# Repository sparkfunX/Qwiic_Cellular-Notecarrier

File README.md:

SparkFun Qwiic Cellular Notecarrier - Blues Wireless
========================================

[*SparkX Qwiic Cellular Notecarrier (SPX-17114)*](https://www.sparkfun.com/products/17114)

When we first saw the Notecard from [Blues Wireless](https://blues.io/) we were intrigued. Unlike most embedded cellular modems, the price of the Blues Wireless card includes a 10 year subscription and 500MB of data. A global cellular module with a built in SIM card with no monthly fee? That sounds enticing. After all, the last thing we need is a hot water heater monitor with a monthly cell phone bill!

The power of Qwiic just keeps expanding! Simply plug the Qwiic Cellular Notecarrier onto any enabled SparkFun Qwiic platforms (currently [over 30](https://www.sparkfun.com/qwiic#products)) and you’ll be able to transmit data anywhere there is cell connectivity with a few lines of Python, Arduino, or JSON. The Blues documentation is superb. All [API calls](https://dev.blues.io/reference/notecard-api/) come with extensive C, Python, and JSON examples. While the Qwiic Cellular focuses on using the I2C bus for communication, USB and Serial can also be used to communicate with the Notecard. We found the USB was handy for immediate gratification and command debugging.

The Notecard module comes with integrated cellular, SIM, onboard GPS, accelerometer, and temperature sensor. The Qwiic Cellular product has everything you need: a carrier board (Blues calls them Notepads), the globally enabled [NB-IoT & LTE-M](https://shop.blues.io/products/note-nbgl-500) M.2 based module (Blues calls them Notecards), and two U.FL cables all assembled and ready to go.

Currently 139 countries are covered with another 33 countries covered by installing a user-supplied external SIM socket and card. See the [Covered Countries](https://dev.blues.io/hardware/notecard-datasheet/note-nbgl-500/#cellular-and-gps-gnss-antenna-requirements) table for more information. Two RF cables connect the Notecard to external SMA connectors for cellular and GPS antennas (sold separately in related items below).

SparkFun labored with love to create this code. Feel like supporting open source hardware? 
Buy a [board](https://www.sparkfun.com/products/17114) from SparkFun!

Repository Contents
-------------------

* **/hardware** - Eagle files

Documentation
--------------

* **[Quick Start Guide](https://dev.blues.io/get-started/quickstart/sparkfun-qwiic-cellular)**
* **[Installing an Arduino Library Guide](https://learn.sparkfun.com/tutorials/installing-an-arduino-library)** - Basic information on how to install an Arduino library.
* **[Notecard API](https://dev.blues.io/reference/notecard-api/introduction/)** - How to interface with Notecard from embedded processor applciations
* **[Notecard Design Files](https://github.com/blues/note-hardware/tree/master/Notecard)** - Models and dimensioned drawings of Notecard

Products that use this Repository
--------------

* [SPX-17114](https://www.sparkfun.com/products/17114)

License Information
-------------------

This product is _**open source**_! 

Please review the LICENSE.md file for license information. 

If you have any questions or concerns on licensing, please contact technical support on our [SparkFun forums](https://forum.sparkfun.com/viewforum.php?f=152).

Distributed as-is; no warranty is given.

- Your friends at SparkFun.

_<COLLABORATION CREDIT>_

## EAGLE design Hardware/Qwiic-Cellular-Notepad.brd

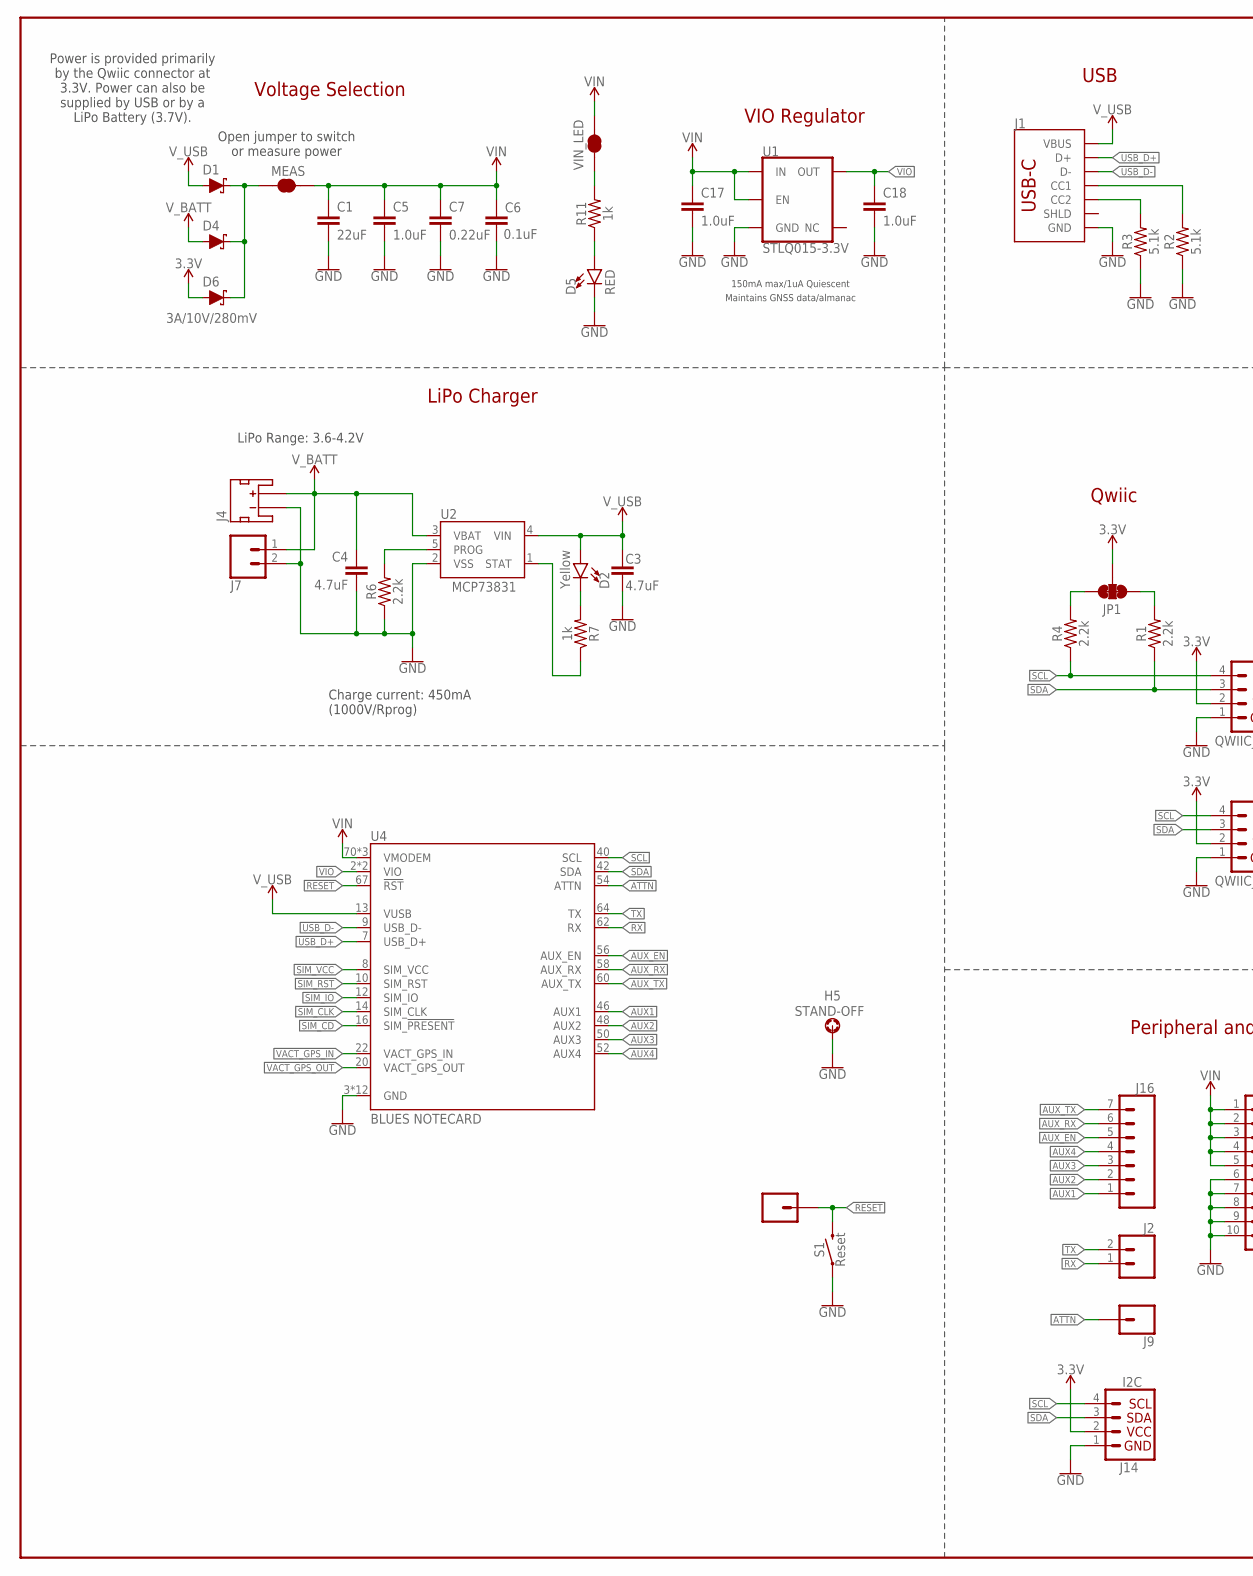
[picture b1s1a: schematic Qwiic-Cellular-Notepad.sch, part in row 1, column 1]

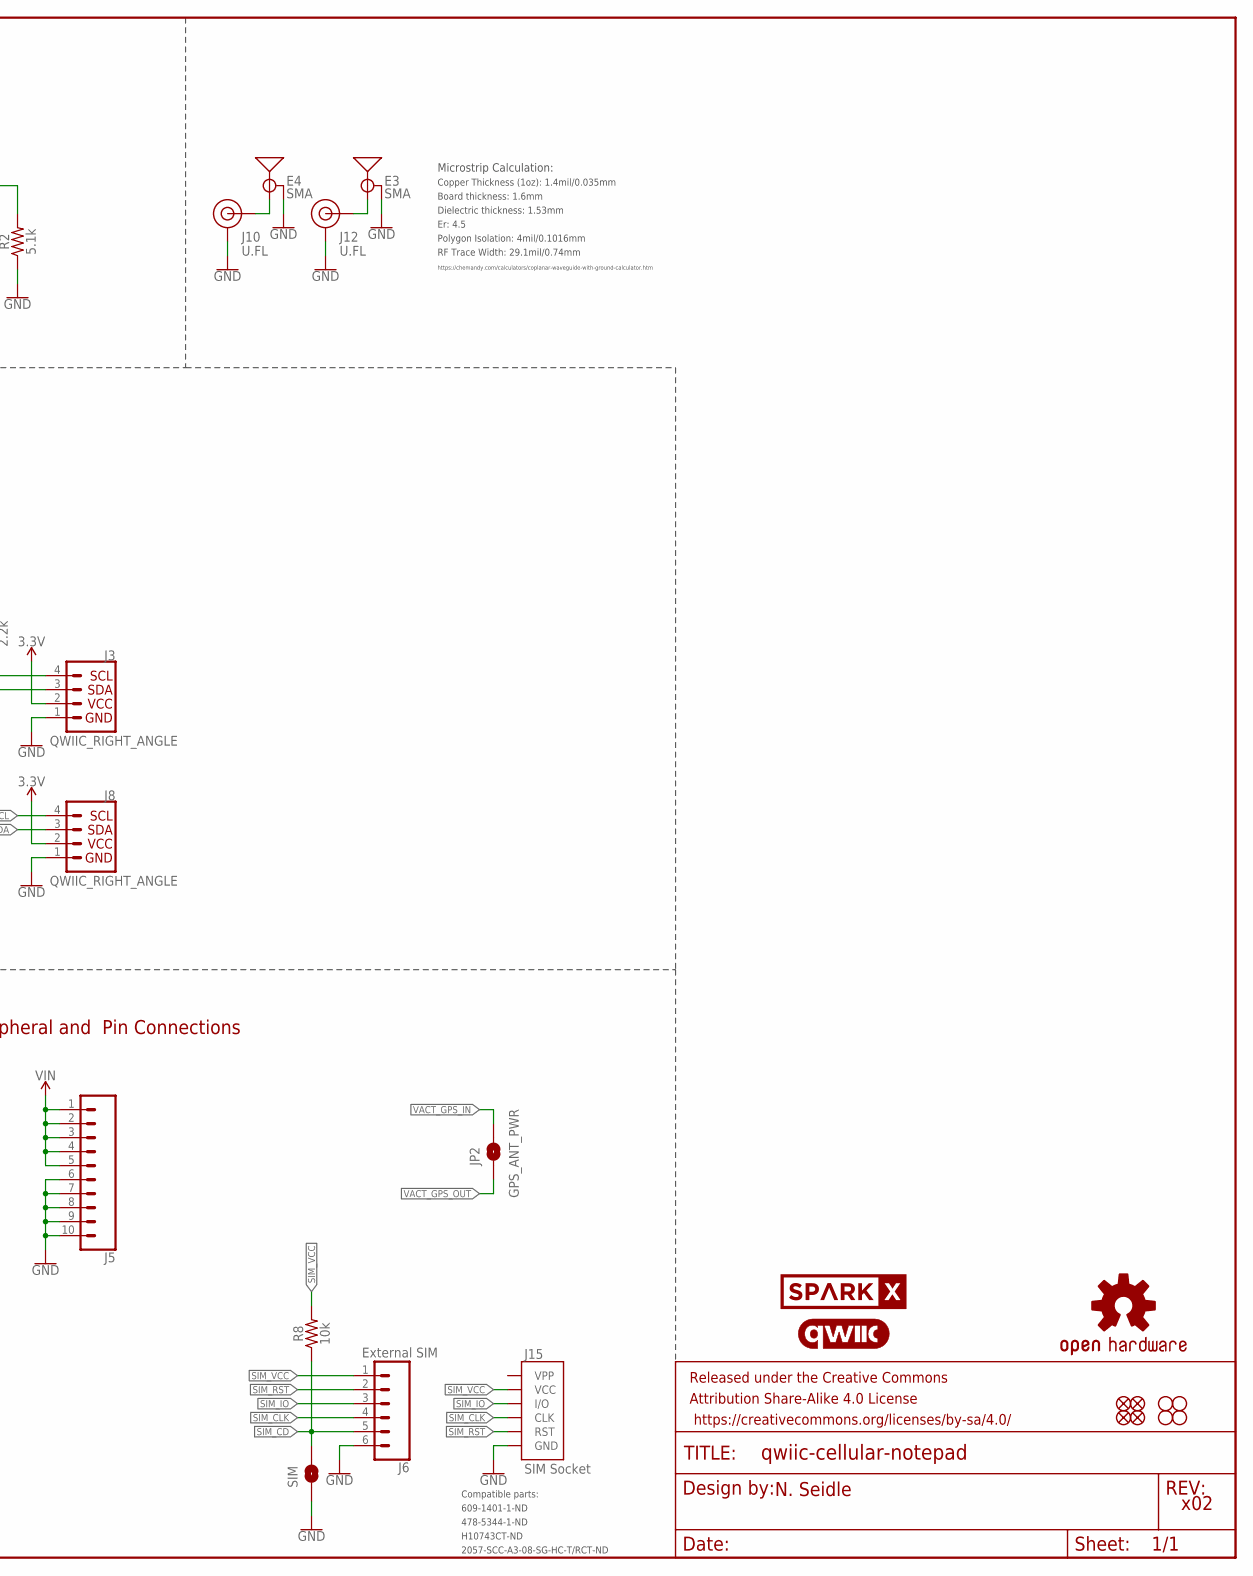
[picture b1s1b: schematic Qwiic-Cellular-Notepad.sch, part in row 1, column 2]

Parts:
C1: 22uF; 1210
C3, C4: 4.7uF; 0603
C5, C17, C18: 1.0uF; 0603
C6: 0.1uF; 0603
C7: 0.22uF; 0603
D1, D4, D6: 3A/10V/280mV; SOD-323
D2: Yellow; LED-0603
D5: RED; LED-0603
E3, E4: SMA; SMA-EDGE-SMD
FD1, FD2, FD3, FD4: FIDUCIALUFIDUCIAL; FIDUCIAL-MICRO
FRAME1: FRAME-LEDGER; CREATIVE_COMMONS
H1, H2, H3, H4: STAND-OFF
H5: STAND-OFF; STAND-OFF-REFLOW-M2.5
J1: USB_C_2-LAYER_PADS; USB-C-16P-2LAYER-PADS
J2, J7: CONN_021X02_NO_SILK; 1X02_NO_SILK
J3, J8: QWIIC_RIGHT_ANGLE; JST04_1MM_RA
J4: JST_2MM_MALE; JST-2-SMD
J5: CONN_10NO_SILK_PTH_FEMALE; 1X10_NO_SILK
J6: External SIM; 1X06_NO_SILK
J9, J13: CONN_01PTH_NO_SILK_YES_STOP; 1X01_NO_SILK
J10, J12: U.FL
J14: I2C; 1X04_NO_SILK
J15: SIM Socket; SIMHOLDER
J16: CONN_07NO_SILK; 1X07_NO_SILK
JP1: JUMPER-SMT_3_2-NC_TRACE_SILK; SMT-JUMPER_3_2-NC_TRACE_SILK
JP2: GPS_ANT_PWR; SMT-JUMPER_2_NO_SILK
LOGO2: QWIIC_LOGO_CONNECTOR; QWIIC_5.5MM
LOGO3: OSHW-LOGOMINI; OSHW-LOGO-MINI
MEAS: JUMPER-COMBO_2_NC_TRACE; COMBO-JUMPER_2_NC_TRACE
R1, R4, R6: 2.2k; 0603
R2, R3: 5.1k; 0603
R7, R11: 1k; 0603
R8: 10k; 0603
S1: Reset; TACTILE_SWITCH_SMD_5.2MM
SIM: JUMPER-SMT_2_NO_SILK; SMT-JUMPER_2_NO_SILK
U1: STLQ015-3.3V; SOT23-5
U2: MCP73831; SOT23-5
U4: BLUES NOTECARD; M.2-CONNECTOR-E
U$56: SPARKX-LOGO4; SPARKX-MEDIUM
VIN_LED: JUMPER-SMT_2_NC_TRACE_SILK; SMT-JUMPER_2_NC_TRACE_SILK

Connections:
3.3V: D6.A, J3.2, J8.2, J14.2, JP1.2
!RESET!: J13.1, S1.3 (2), S1.4 (2), U4.67 (!RST!)
ATTN: J9.1, U4.54 (ATTN)
AUX1: J16.1, U4.46 (AUX1)
AUX2: J16.2, U4.48 (AUX2)
AUX3: J16.3, U4.50 (AUX3)
AUX4: J16.4, U4.52 (AUX4)
AUX_EN: J16.5, U4.56 (AUX_EN)
AUX_RX: J16.6, U4.58 (AUX_RX)
AUX_TX: J16.7, U4.60 (AUX_TX)
CHG_LED: R7.1, U2.1 (STAT)
GND: C1.2, C3.2, C4.2, C5.2, C6.2, C7.2, C17.2, C18.2, D5.C, E3.GND@0 (GND), E3.GND@1 (GND), E4.GND@0 (GND), E4.GND@1 (GND), H5.1, J1.GND, J1.GND2 (GND), J3.1, J4.1 (-), J5.6, J5.7, J5.8, J5.9, J5.10, J6.6, J7.2, J8.1, J10.1 (GND), J10.2 (GND), J12.1 (GND), J12.2 (GND), J14.1, J15.C5 (GND), R2.1, R3.1, R6.1, S1.1, S1.2 (1), SIM.1, U1.2 (GND), U2.2 (VSS), U4.3 (GND), U4.5 (GND), U4.6 (GND), U4.11 (GND), U4.18 (GND), U4.33 (GND), U4.39 (GND), U4.45 (GND), U4.51 (GND), U4.57 (GND), U4.71 (GND), U4.73 (GND)
unnamed: JP1.3, R4.2
unnamed: JP1.1, R1.2
unnamed: D2.C, R7.2
unnamed: D5.A, R11.1
unnamed: R11.2, VIN_LED.1
unnamed: R6.2, U2.5 (PROG)
unnamed: J1.A5 (CC1), R2.2
unnamed: J1.B5 (CC2), R3.2
RF_GPS: E4.SIG (SIGNAL), J10.FEED (SIGNAL)
RF_LTE: E3.SIG (SIGNAL), J12.FEED (SIGNAL)
RX: J2.1, U4.62 (RX)
SCL: J3.4, J8.4, J14.4, R4.1, U4.40 (SCL)
SDA: J3.3, J8.3, J14.3, R1.1, U4.42 (SDA)
SIM_!CD!: J6.5, R8.1, SIM.2, U4.16 (SIM_!PRESENT!)
SIM_CLK: J6.4, J15.C3 (CLK), U4.14 (SIM_CLK)
SIM_IO: J6.3, J15.C7 (I/O), U4.12 (SIM_IO)
SIM_RST: J6.2, J15.C2 (RST), U4.10 (SIM_RST)
SIM_VCC: J6.1, J15.C1 (VCC), R8.2, U4.8 (SIM_VCC)
TX: J2.2, U4.64 (TX)
USB_D+: J1.A6 (D+), J1.B6 (D+), U4.7 (USB_D+)
USB_D-: J1.A7 (D-), J1.B7 (D-), U4.9 (USB_D-)
VACT_GPS_IN: JP2.2, U4.22 (VACT_GPS_IN)
VACT_GPS_OUT: JP2.1, U4.20 (VACT_GPS_OUT)
VIN: C1.1, C5.1, C6.1, C7.1, C17.1, J5.1, J5.2, J5.3, J5.4, J5.5, MEAS.2, MEAS.4 (2), U1.1 (IN), U1.3 (EN), U4.70 (VMODEM), U4.72 (VMODEM), U4.74 (VMODEM), VIN_LED.2
VIN1: D1.C, D4.C, D6.C, MEAS.1, MEAS.3 (1)
VIO: C18.1, U1.5 (OUT), U4.2 (VIO), U4.4 (VIO)
V_BATT: C4.1, D4.A, J4.2 (+), J7.1, U2.3 (VBAT)
V_USB: C3.1, D1.A, D2.A, J1.VBUS1 (VBUS), J1.VBUS2 (VBUS), U2.4 (VIN), U4.13 (VUSB)

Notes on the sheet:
USB
Peripheral and Pin Connections
Qwiic
Voltage Selection
LiPo Charger
LiPo Range: 3.6-4.2V
Charge current: 450mA (1000V/Rprog)
Open jumper to switch or measure power
N. Seidle
x02
Power is provided primarily by the Qwiic connector at 3.3V. Power can also be supplied by USB or by a LiPo Battery (3.7V).
Board thickness: 1.6mm
Er: 4.5
Copper Thickness (1oz): 1.4mil/0.035mm
RF Trace Width: 29.1mil/0.74mm
Polygon Isolation: 4mil/0.1016mm
Dielectric thickness: 1.53mm
https://chemandy.com/calculators/coplanar-waveguide-with-ground-calculator.htm
Microstrip Calculation:
Compatible parts:
609-1401-1-ND
478-5344-1-ND
H10743CT-ND
2057-SCC-A3-08-SG-HC-T/RCT-ND
VIO Regulator
150mA max/1uA Quiescent
Maintains GNSS data/almanac

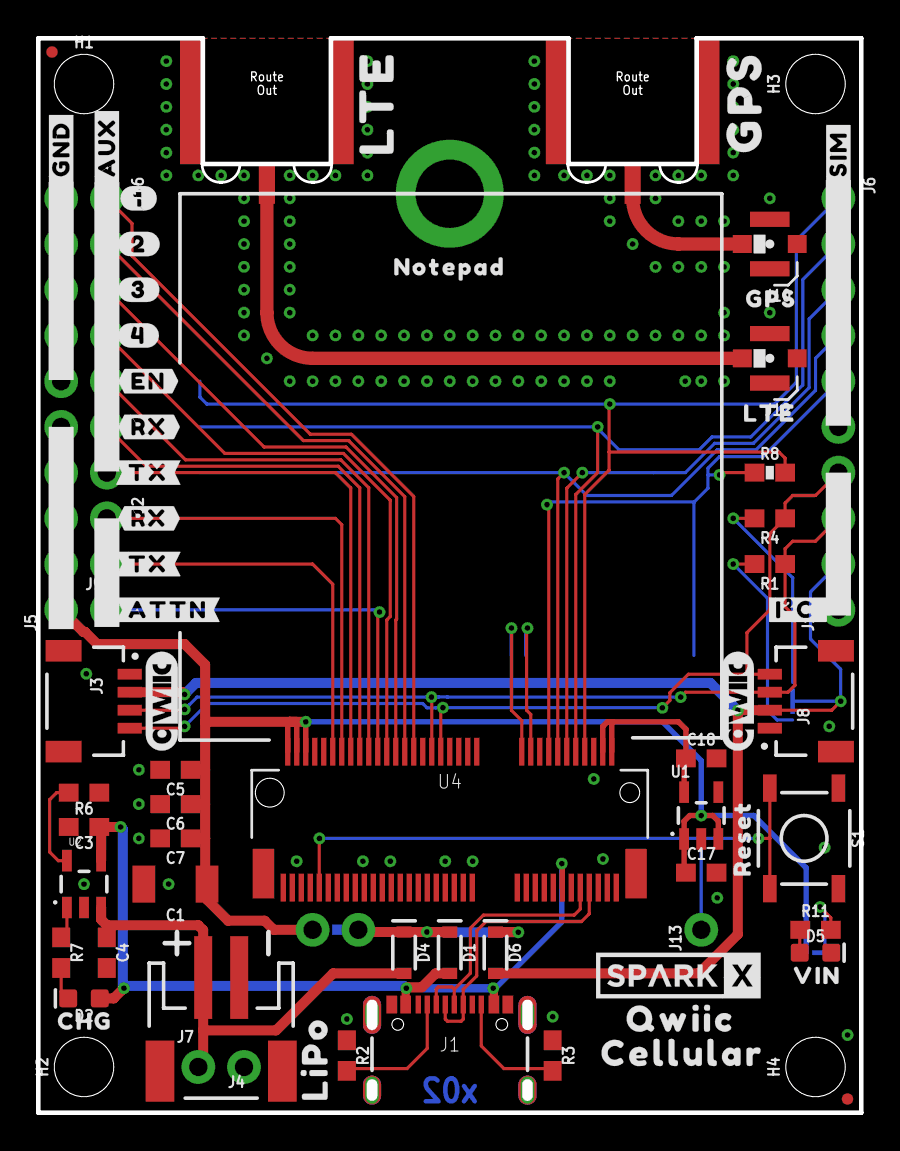
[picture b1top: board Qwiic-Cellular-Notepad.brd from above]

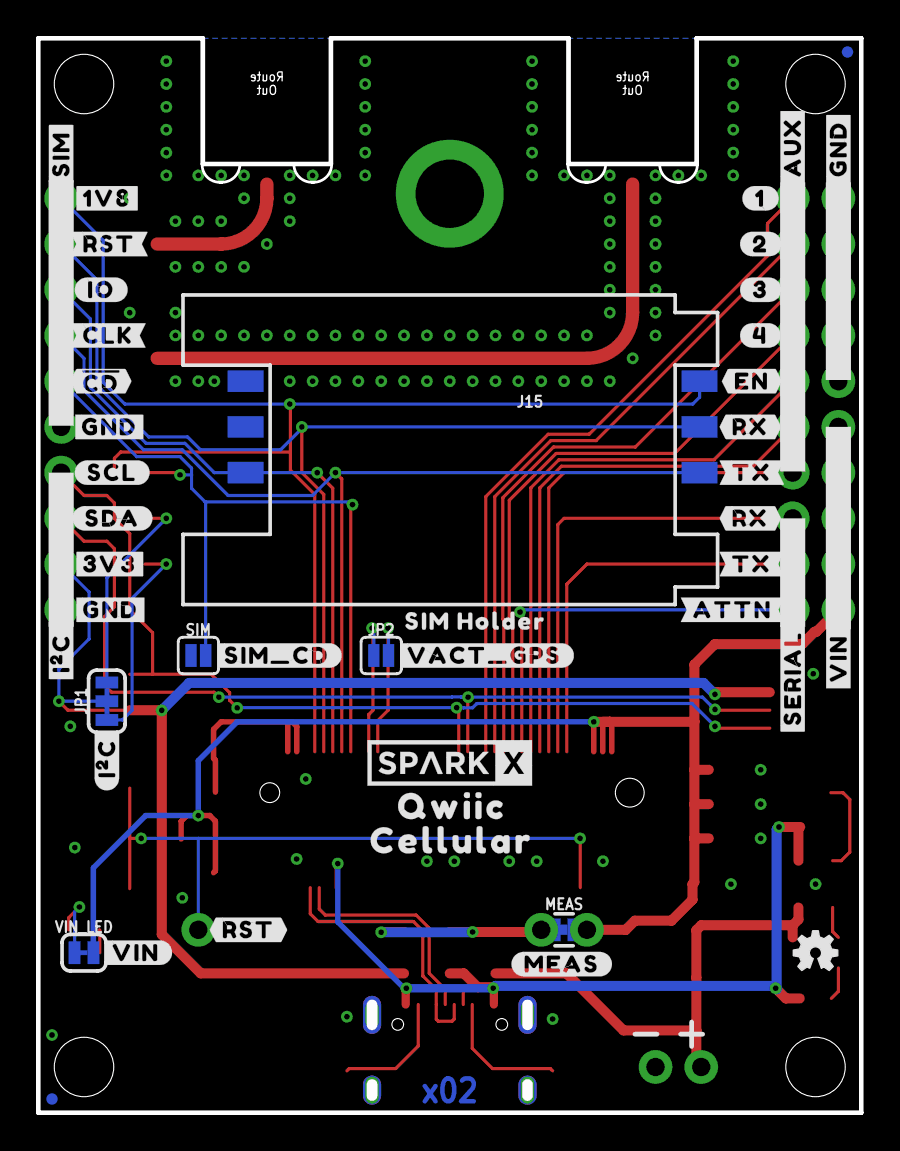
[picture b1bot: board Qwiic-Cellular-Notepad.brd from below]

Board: 2 copper layers, 45.7 x 59.7 mm, 122 parts (45 on the bottom side), 40 nets.

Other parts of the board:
LOGO5: QWIIC_LOGO_CONNECTOR; QWIIC_5.5MM
U$1, U$41: #1#1
U$2: #3V3#2
U$3, U$18, U$22: #GND#0
U$4, U$42: #2#2
U$5, U$43: #3#3
U$6, U$44: #4#4
U$7: GPS_0
U$8: #SERIAL#1
U$9, U$53: #I�C_#0
U$10: #I�C#0
U$11, U$40: #AUX#0
U$12: LTE_1
U$13: #GND#3
U$14, U$46: #RX#6
U$15: LIPO0
U$16, U$47: #TX#5
U$17: #SCL#1
U$19, U$45: #EN#0
U$20: NOTEPAD0
U$21: #SDA#0
U$23: #VIN#0
U$24: #VACT_GPS#0
U$25: #SIM_CD#0
U$26, U$31: QWIIC0
U$27: SIM_HOLDER0
U$28: #MEAS#3
U$29, U$32: CELLULAR1
U$30: #RST#0
U$33: #VIN#1
U$34: ##CD##1
U$35: #1V8#4
U$36: #CLK#3
U$37: #IO#2
U$38: #RST#5
U$39, U$51: #SIM#0
U$48, U$52: #RX#0
U$49, U$54: #TX#1
U$50, U$55: #ATTN#2
U$57: SPARKX-LOGO4; SPARKX-MEDIUM
U$58: GPS0
U$59: LTE1
U$92: RESET1
U$94: VIN1
U$96: CHG1

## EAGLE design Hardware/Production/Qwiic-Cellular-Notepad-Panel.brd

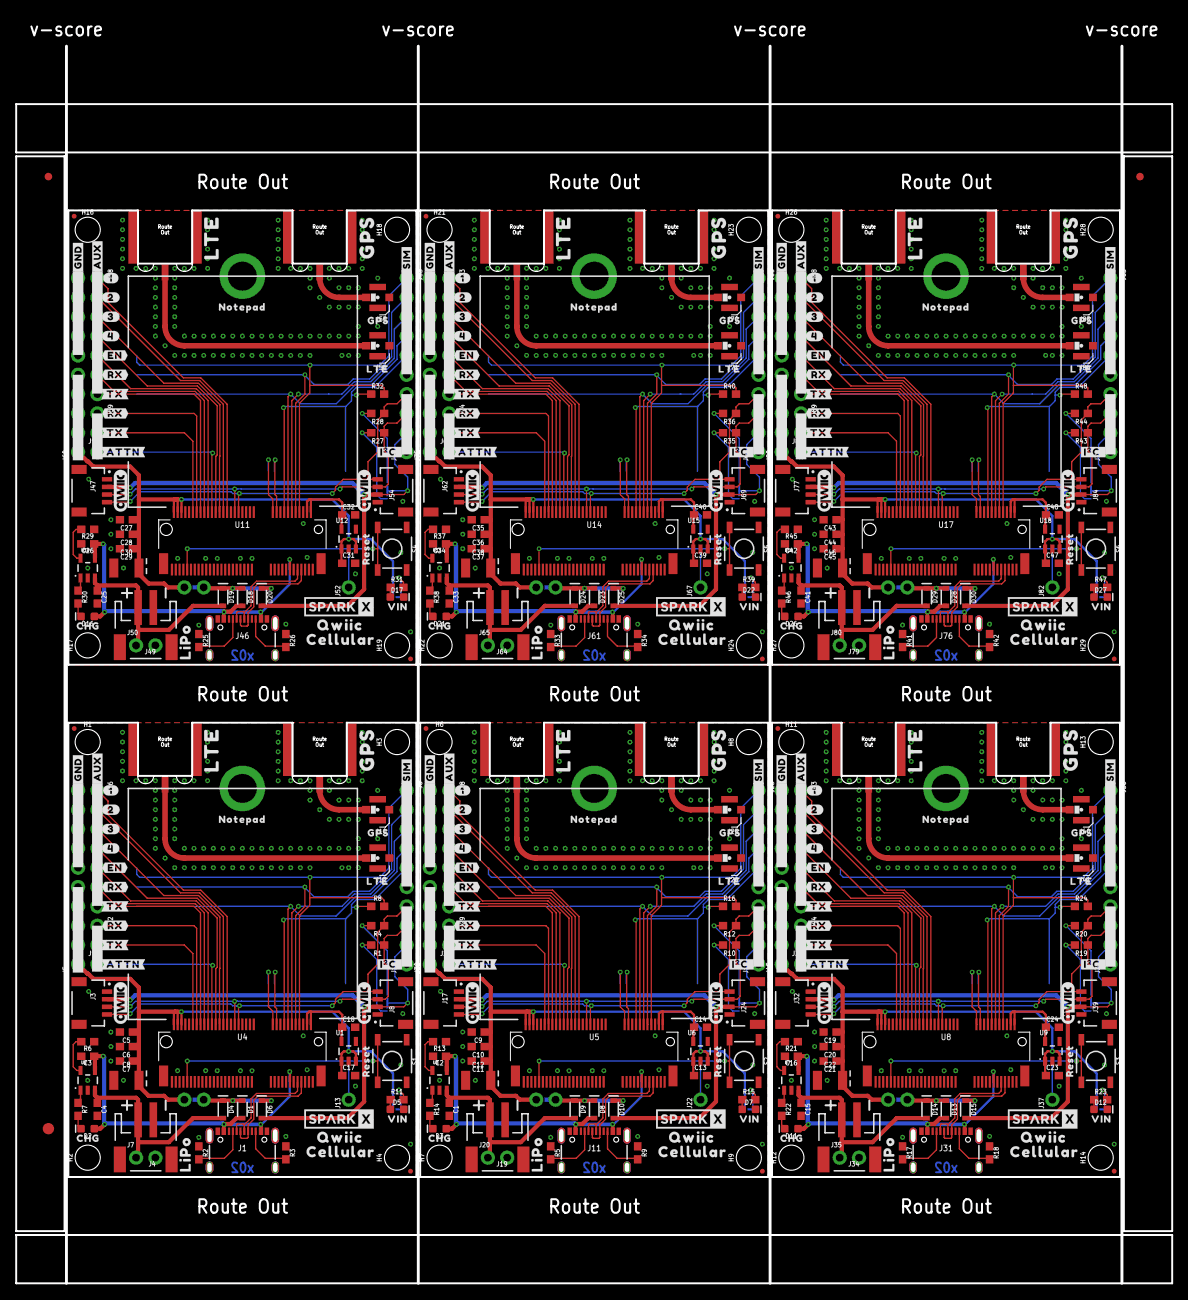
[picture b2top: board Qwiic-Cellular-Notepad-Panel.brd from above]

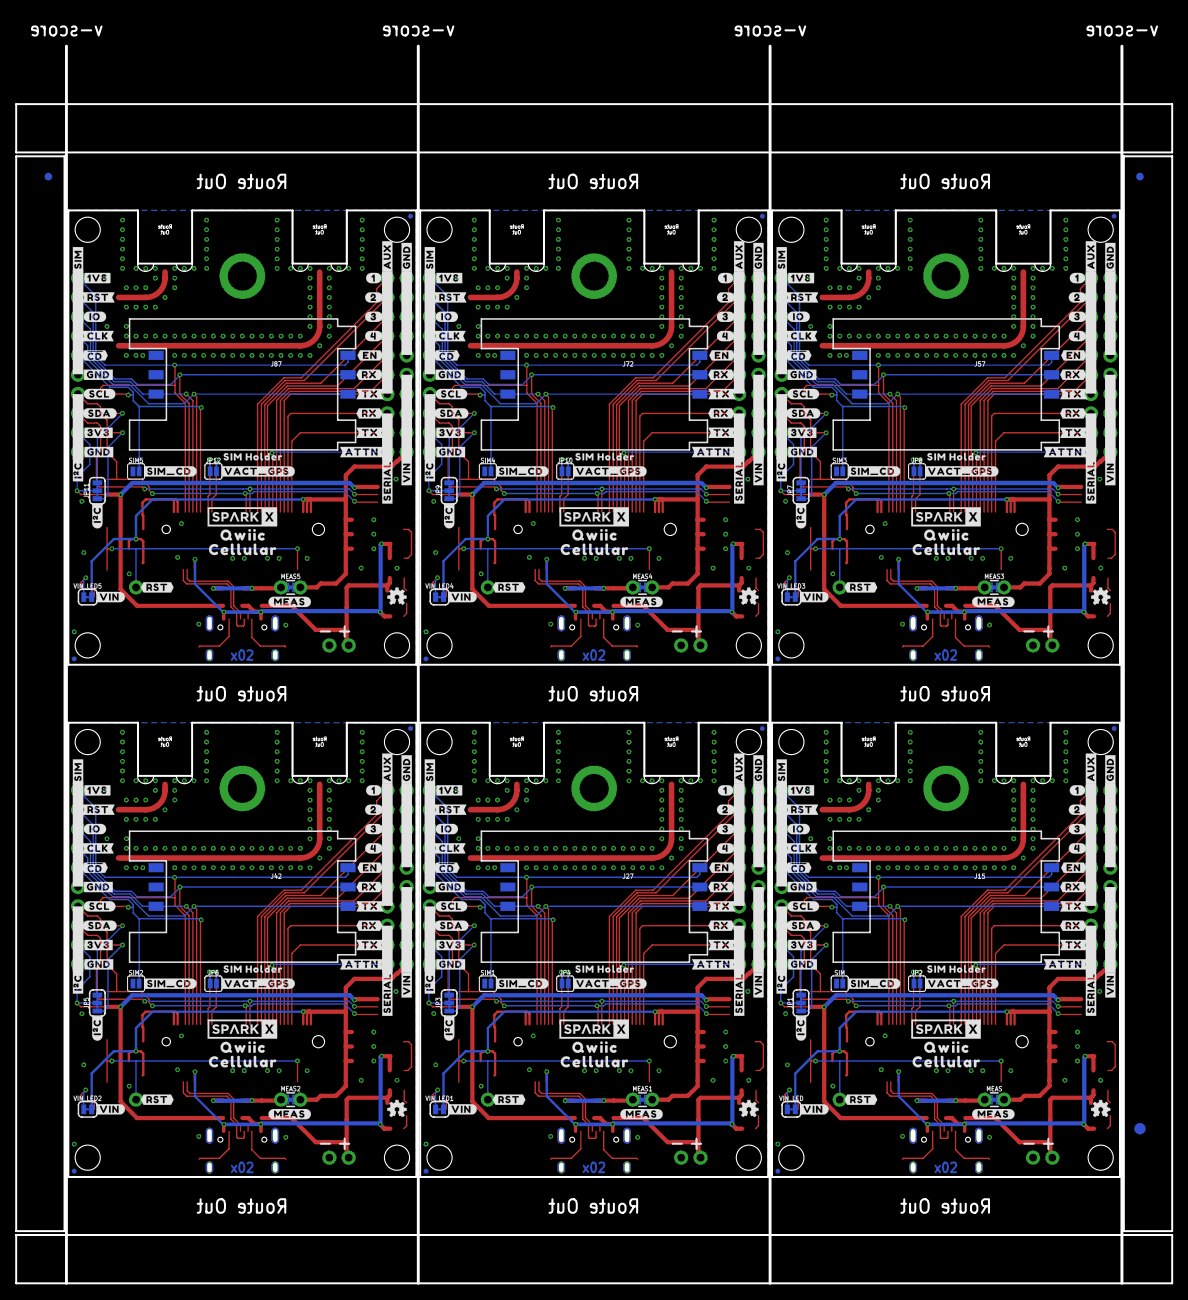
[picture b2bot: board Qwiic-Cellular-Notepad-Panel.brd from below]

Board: 2 copper layers, 151.9 x 162.6 mm, 732 parts (273 on the bottom side), 240 nets.

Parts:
C1, C2, C3, C4, C15, C16, C25, C26, C33, C34, C41, C42: 4.7uF; 0603
C5, C9, C13, C14, C17, C18, C19, C23, C24, C27, C31, C32, C35, C39, C40, C43, C47, C48: 1.0uF; 0603
C6, C10, C20, C28, C36, C44: 0.1uF; 0603
C7, C11, C21, C29, C37, C45: 0.22uF; 0603
C8, C12, C22, C30, C38, C46: 68uF; EIA3528
D1, D4, D6, D8, D9, D10, D13, D14, D15, D18, D19, D20, D23, D24, D25, D28, D29, D30: 3A/10V/280mV; SOD-323
D2, D3, D11, D16, D21, D26: Yellow; LED-0603
D5, D7, D12, D17, D22, D27: RED; LED-0603
E1, E2, E3, E4, E5, E6, E7, E8, E9, E10, E11, E12: SMA; SMA-EDGE-SMD
E$1, E$2, E$3, E$4: FIDUCIAL-1X2
E$5, E$6: FIDUCIAL-1.5X3
FD1, FD2, FD3, FD4, FD5, FD6, FD7, FD8, FD9, FD10, FD11, FD12, FD13, FD14, FD15, FD16, FD17, FD18, FD19, FD20, FD21, FD22, FD23, FD24: FIDUCIALUFIDUCIAL; FIDUCIAL-MICRO
H1, H2, H3, H4, H6, H7, H8, H9, H11, H12, H13, H14, H16, H17, H18, H19, H21, H22, H23, H24, H26, H27, H28, H29: STAND-OFF
H5, H10, H15, H20, H25, H30: STAND-OFF; STAND-OFF-REFLOW-M2.5
J1, J11, J31, J46, J61, J76: USB-C-16P-2LAYER-PADS
J2, J7, J20, J29, J35, J44, J50, J59, J65, J74, J80, J89: 1X02_NO_SILK
J3, J8, J17, J24, J32, J39, J47, J54, J62, J69, J77, J84: QWIIC_RIGHT_ANGLE; JST04_1MM_RA
J4, J19, J34, J49, J64, J79: JST-2-SMD
J5, J30, J45, J60, J75, J90: 1X10_NO_SILK
J6, J23, J38, J53, J68, J83: External SIM; 1X06_NO_SILK
J9, J13, J21, J22, J36, J37, J51, J52, J66, J67, J81, J82: 1X01_NO_SILK
J10, J12, J25, J26, J40, J41, J55, J56, J70, J71, J85, J86: U.FL
J14, J18, J33, J48, J63, J78: I2C; 1X04_NO_SILK
J15, J27, J42, J57, J72, J87: SIM Socket; SIMHOLDER
J16, J28, J43, J58, J73, J88: 1X07_NO_SILK
JP1, JP3, JP5, JP7, JP9, JP11: SMT-JUMPER_3_2-NC_TRACE_SILK
JP2, JP4, JP6, JP8, JP10, JP12: GPS_ANT_PWR; SMT-JUMPER_2_NO_SILK
LOGO1, LOGO2, LOGO5, LOGO6, LOGO7, LOGO9, LOGO10, LOGO12, LOGO13, LOGO15, LOGO16, LOGO18: QWIIC_LOGO_CONNECTOR; QWIIC_5.5MM
LOGO3, LOGO4, LOGO8, LOGO11, LOGO14, LOGO17: OSHW-LOGOMINI; OSHW-LOGO-MINI
MEAS, MEAS1, MEAS2, MEAS3, MEAS4, MEAS5: COMBO-JUMPER_2_NC_TRACE
R1, R4, R6, R10, R12, R13, R19, R20, R21, R27, R28, R29, R35, R36, R37, R43, R44, R45: 2.2k; 0603
R2, R3, R5, R9, R17, R18, R25, R26, R33, R34, R41, R42: 5.1k; 0603
R7, R11, R14, R15, R22, R23, R30, R31, R38, R39, R46, R47: 1k; 0603
R8, R16, R24, R32, R40, R48: 10k; 0603
S1, S2, S3, S4, S5, S6: Reset; TACTILE_SWITCH_SMD_5.2MM
SIM, SIM1, SIM2, SIM3, SIM4, SIM5: SMT-JUMPER_2_NO_SILK
U1, U6, U9, U12, U15, U18: STLQ015-3.3V; SOT23-5
U2, U3, U7, U10, U13, U16: MCP73831; SOT23-5
U4, U5, U8, U11, U14, U17: BLUES NOTECARD; M.2-CONNECTOR-E
U$1, U$41, U$83, U$111, U$148, U$173, U$210, U$235, U$272, U$297, U$334, U$359: #1#1
U$2, U$74, U$139, U$201, U$263, U$325: #3V3#2
U$3, U$18, U$22, U$63, U$73, U$109, U$128, U$138, U$171, U$190, U$200, U$233, U$252, U$262, U$295, U$314, U$324, U$357: #GND#0
U$4, U$42, U$84, U$112, U$149, U$174, U$211, U$236, U$273, U$298, U$335, U$360: #2#2
U$5, U$43, U$85, U$113, U$150, U$175, U$212, U$237, U$274, U$299, U$336, U$361: #3#3
U$6, U$44, U$86, U$114, U$151, U$176, U$213, U$238, U$275, U$300, U$337, U$362: #4#4
U$7, U$107, U$169, U$231, U$293, U$355: GPS_0
U$8, U$104, U$166, U$228, U$290, U$352: #SERIAL#1
U$9, U$53, U$106, U$122, U$168, U$184, U$230, U$246, U$292, U$308, U$354, U$370: #I�C_#0
U$10, U$105, U$167, U$229, U$291, U$353: #I�C#0
U$11, U$40, U$87, U$110, U$152, U$172, U$214, U$234, U$276, U$296, U$338, U$358: #AUX#0
U$12, U$108, U$170, U$232, U$294, U$356: LTE_1
U$13, U$75, U$140, U$202, U$264, U$326: #GND#3
U$14, U$46, U$88, U$116, U$153, U$178, U$215, U$240, U$277, U$302, U$339, U$364: #RX#6
U$15, U$64, U$129, U$191, U$253, U$315: LIPO0
U$16, U$47, U$89, U$117, U$154, U$179, U$216, U$241, U$278, U$303, U$340, U$365: #TX#5
U$17, U$76, U$141, U$203, U$265, U$327: #SCL#1
U$19, U$45, U$90, U$115, U$155, U$177, U$217, U$239, U$279, U$301, U$341, U$363: #EN#0
U$20, U$97, U$159, U$221, U$283, U$345: NOTEPAD0
U$21, U$77, U$142, U$204, U$266, U$328: #SDA#0
U$23, U$91, U$156, U$218, U$280, U$342: #VIN#0
U$24, U$78, U$143, U$205, U$267, U$329: #VACT_GPS#0
U$25, U$79, U$144, U$206, U$268, U$330: #SIM_CD#0
U$26, U$31, U$82, U$93, U$147, U$157, U$209, U$219, U$271, U$281, U$333, U$343: QWIIC0
U$27, U$80, U$145, U$207, U$269, U$331: SIM_HOLDER0
U$28, U$65, U$130, U$192, U$254, U$316: #MEAS#3
U$29, U$32, U$81, U$95, U$146, U$158, U$208, U$220, U$270, U$282, U$332, U$344: CELLULAR1
U$30, U$66, U$131, U$193, U$255, U$317: #RST#0
U$33, U$67, U$132, U$194, U$256, U$318: #VIN#1
U$34, U$99, U$161, U$223, U$285, U$347: ##CD##1
U$35, U$98, U$160, U$222, U$284, U$346: #1V8#4
U$36, U$100, U$162, U$224, U$286, U$348: #CLK#3
U$37, U$101, U$163, U$225, U$287, U$349: #IO#2
U$38, U$102, U$164, U$226, U$288, U$350: #RST#5
U$39, U$51, U$103, U$121, U$165, U$183, U$227, U$245, U$289, U$307, U$351, U$369: #SIM#0
U$48, U$52, U$68, U$118, U$133, U$180, U$195, U$242, U$257, U$304, U$319, U$366: #RX#0
U$49, U$54, U$69, U$119, U$134, U$181, U$196, U$243, U$258, U$305, U$320, U$367: #TX#1
U$50, U$55, U$70, U$120, U$135, U$182, U$197, U$244, U$259, U$306, U$321, U$368: #ATTN#2
U$56, U$57, U$123, U$124, U$185, U$186, U$247, U$248, U$309, U$310, U$371, U$372: SPARKX-LOGO4; SPARKX-MEDIUM
U$58, U$71, U$136, U$198, U$260, U$322: GPS0
U$59, U$72, U$137, U$199, U$261, U$323: LTE1
U$60, U$92, U$125, U$187, U$249, U$311: RESET1
U$61, U$94, U$126, U$188, U$250, U$312: VIN1
U$62, U$96, U$127, U$189, U$251, U$313: CHG1
VIN_LED, VIN_LED1, VIN_LED2, VIN_LED3, VIN_LED4, VIN_LED5: SMT-JUMPER_2_NC_TRACE_SILK

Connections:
3.3V: D6.A, J3.2, J8.2, J14.2, JP1.2
3.3V1: D10.A, J17.2, J18.2, J24.2, JP3.2
3.3V2: D15.A, J32.2, J33.2, J39.2, JP5.2
3.3V3: D20.A, J47.2, J48.2, J54.2, JP7.2
3.3V4: D25.A, J62.2, J63.2, J69.2, JP9.2
3.3V5: D30.A, J77.2, J78.2, J84.2, JP11.2
!RESET!: J13.1, S1.3, S1.4, U4.67
!RESET!1: J22.1, S2.3, S2.4, U5.67
!RESET!2: J37.1, S3.3, S3.4, U8.67
!RESET!3: J52.1, S4.3, S4.4, U11.67
!RESET!4: J67.1, S5.3, S5.4, U14.67
!RESET!5: J82.1, S6.3, S6.4, U17.67
ATTN: J9.1, U4.54
ATTN1: J21.1, U5.54
ATTN2: J36.1, U8.54
ATTN3: J51.1, U11.54
ATTN4: J66.1, U14.54
ATTN5: J81.1, U17.54
AUX1: J16.1, U4.46
AUX2: J16.2, U4.48
AUX3: J16.3, U4.50
AUX4: J16.4, U4.52
AUX5: J28.1, U5.46
AUX6: J28.2, U5.48
AUX7: J28.3, U5.50
AUX8: J28.4, U5.52
AUX9: J43.1, U8.46
AUX10: J43.2, U8.48
AUX11: J43.3, U8.50
AUX12: J43.4, U8.52
AUX13: J58.1, U11.46
AUX14: J58.2, U11.48
AUX15: J58.3, U11.50
AUX16: J58.4, U11.52
AUX17: J73.1, U14.46
AUX18: J73.2, U14.48
AUX19: J73.3, U14.50
AUX20: J73.4, U14.52
AUX21: J88.1, U17.46
AUX22: J88.2, U17.48
AUX23: J88.3, U17.50
AUX24: J88.4, U17.52
AUX_EN: J16.5, U4.56
AUX_EN1: J28.5, U5.56
AUX_EN2: J43.5, U8.56
AUX_EN3: J58.5, U11.56
AUX_EN4: J73.5, U14.56
AUX_EN5: J88.5, U17.56
AUX_RX: J16.6, U4.58
AUX_RX1: J28.6, U5.58
AUX_RX2: J43.6, U8.58
AUX_RX3: J58.6, U11.58
AUX_RX4: J73.6, U14.58
AUX_RX5: J88.6, U17.58
AUX_TX: J16.7, U4.60
AUX_TX1: J28.7, U5.60
AUX_TX2: J43.7, U8.60
AUX_TX3: J58.7, U11.60
AUX_TX4: J73.7, U14.60
AUX_TX5: J88.7, U17.60
CHG_LED: R7.1, U2.1
CHG_LED1: R14.1, U3.1
CHG_LED2: R22.1, U7.1
CHG_LED3: R30.1, U10.1
CHG_LED4: R38.1, U13.1
CHG_LED5: R46.1, U16.1
GND: C3.2, C4.2, C5.2, C6.2, C7.2, C8.C, C17.2, C18.2, D5.C, E3.GND@0, E3.GND@1, E4.GND@0, E4.GND@1, H5.1, J1.GND, J1.GND2, J3.1, J4.1, J5.6, J5.7, J5.8, J5.9, J5.10, J6.6, J7.2, J8.1, J10.1, J10.2, J12.1, J12.2, J14.1, J15.C5, R2.1, R3.1, R6.1, S1.1, S1.2, SIM.1, U1.2, U2.2, U4.3, U4.5, U4.6, U4.11, U4.18, U4.33, U4.39, U4.45, U4.51, U4.57, U4.71, U4.73
GND1: C1.2, C2.2, C9.2, C10.2, C11.2, C12.C, C13.2, C14.2, D7.C, E1.GND@0, E1.GND@1, E2.GND@0, E2.GND@1, H10.1, J11.GND, J11.GND2, J17.1, J18.1, J19.1, J20.2, J23.6, J24.1, J25.1, J25.2, J26.1, J26.2, J27.C5, J30.6, J30.7, J30.8, J30.9, J30.10, R5.1, R9.1, R13.1, S2.1, S2.2, SIM1.1, U3.2, U5.3, U5.5, U5.6, U5.11, U5.18, U5.33, U5.39, U5.45, U5.51, U5.57, U5.71, U5.73, U6.2
GND2: C15.2, C16.2, C19.2, C20.2, C21.2, C22.C, C23.2, C24.2, D12.C, E5.GND@0, E5.GND@1, E6.GND@0, E6.GND@1, H15.1, J31.GND, J31.GND2, J32.1, J33.1, J34.1, J35.2, J38.6, J39.1, J40.1, J40.2, J41.1, J41.2, J42.C5, J45.6, J45.7, J45.8, J45.9, J45.10, R17.1, R18.1, R21.1, S3.1, S3.2, SIM2.1, U7.2, U8.3, U8.5, U8.6, U8.11, U8.18, U8.33, U8.39, U8.45, U8.51, U8.57, U8.71, U8.73, U9.2
GND3: C25.2, C26.2, C27.2, C28.2, C29.2, C30.C, C31.2, C32.2, D17.C, E7.GND@0, E7.GND@1, E8.GND@0, E8.GND@1, H20.1, J46.GND, J46.GND2, J47.1, J48.1, J49.1, J50.2, J53.6, J54.1, J55.1, J55.2, J56.1, J56.2, J57.C5, J60.6, J60.7, J60.8, J60.9, J60.10, R25.1, R26.1, R29.1, S4.1, S4.2, SIM3.1, U10.2, U11.3, U11.5, U11.6, U11.11, U11.18, U11.33, U11.39, U11.45, U11.51, U11.57, U11.71, U11.73, U12.2
GND4: C33.2, C34.2, C35.2, C36.2, C37.2, C38.C, C39.2, C40.2, D22.C, E9.GND@0, E9.GND@1, E10.GND@0, E10.GND@1, H25.1, J61.GND, J61.GND2, J62.1, J63.1, J64.1, J65.2, J68.6, J69.1, J70.1, J70.2, J71.1, J71.2, J72.C5, J75.6, J75.7, J75.8, J75.9, J75.10, R33.1, R34.1, R37.1, S5.1, S5.2, SIM4.1, U13.2, U14.3, U14.5, U14.6, U14.11, U14.18, U14.33, U14.39, U14.45, U14.51, U14.57, U14.71, U14.73, U15.2
GND5: C41.2, C42.2, C43.2, C44.2, C45.2, C46.C, C47.2, C48.2, D27.C, E11.GND@0, E11.GND@1, E12.GND@0, E12.GND@1, H30.1, J76.GND, J76.GND2, J77.1, J78.1, J79.1, J80.2, J83.6, J84.1, J85.1, J85.2, J86.1, J86.2, J87.C5, J90.6, J90.7, J90.8, J90.9, J90.10, R41.1, R42.1, R45.1, S6.1, S6.2, SIM5.1, U16.2, U17.3, U17.5, U17.6, U17.11, U17.18, U17.33, U17.39, U17.45, U17.51, U17.57, U17.71, U17.73, U18.2
unnamed: J11.A5, R5.2
unnamed: JP1.3, R4.2
unnamed: JP1.1, R1.2
unnamed: D2.C, R7.2
unnamed: D5.A, R11.1
unnamed: R11.2, VIN_LED.1
unnamed: R6.2, U2.5
unnamed: J11.B5, R9.2
unnamed: JP3.3, R12.2
unnamed: J1.A5, R2.2
unnamed: J1.B5, R3.2
unnamed: JP3.1, R10.2
unnamed: R13.2, U3.5
unnamed: D3.C, R14.2
unnamed: R15.2, VIN_LED1.1
unnamed: D7.A, R15.1
unnamed: J31.A5, R17.2
unnamed: J31.B5, R18.2
unnamed: JP5.3, R20.2
unnamed: JP5.1, R19.2
unnamed: R21.2, U7.5
unnamed: D11.C, R22.2
unnamed: R23.2, VIN_LED2.1
unnamed: D12.A, R23.1
unnamed: J46.A5, R25.2
unnamed: J46.B5, R26.2
unnamed: JP7.3, R28.2
unnamed: JP7.1, R27.2
unnamed: R29.2, U10.5
unnamed: D16.C, R30.2
unnamed: R31.2, VIN_LED3.1
unnamed: D17.A, R31.1
unnamed: J61.A5, R33.2
unnamed: J61.B5, R34.2
unnamed: JP9.3, R36.2
unnamed: JP9.1, R35.2
unnamed: R37.2, U13.5
unnamed: D21.C, R38.2
unnamed: R39.2, VIN_LED4.1
unnamed: D22.A, R39.1
unnamed: J76.A5, R41.2
unnamed: J76.B5, R42.2
unnamed: JP11.3, R44.2
unnamed: JP11.1, R43.2
unnamed: R45.2, U16.5
unnamed: D26.C, R46.2
unnamed: R47.2, VIN_LED5.1
unnamed: D27.A, R47.1
RF_GPS: E4.SIG, J10.FEED
RF_GPS1: E2.SIG, J25.FEED
RF_GPS2: E6.SIG, J40.FEED
RF_GPS3: E8.SIG, J55.FEED
RF_GPS4: E10.SIG, J70.FEED
RF_GPS5: E12.SIG, J85.FEED
RF_LTE: E3.SIG, J12.FEED
RF_LTE1: E1.SIG, J26.FEED
RF_LTE2: E5.SIG, J41.FEED
RF_LTE3: E7.SIG, J56.FEED
RF_LTE4: E9.SIG, J71.FEED
RF_LTE5: E11.SIG, J86.FEED
RX: J2.1, U4.62
RX1: J29.1, U5.62
RX2: J44.1, U8.62
RX3: J59.1, U11.62
RX4: J74.1, U14.62
RX5: J89.1, U17.62
SCL: J3.4, J8.4, J14.4, R4.1, U4.40
SCL1: J17.4, J18.4, J24.4, R12.1, U5.40
SCL2: J32.4, J33.4, J39.4, R20.1, U8.40
SCL3: J47.4, J48.4, J54.4, R28.1, U11.40
SCL4: J62.4, J63.4, J69.4, R36.1, U14.40
SCL5: J77.4, J78.4, J84.4, R44.1, U17.40
SDA: J3.3, J8.3, J14.3, R1.1, U4.42
SDA1: J17.3, J18.3, J24.3, R10.1, U5.42
SDA2: J32.3, J33.3, J39.3, R19.1, U8.42
SDA3: J47.3, J48.3, J54.3, R27.1, U11.42
SDA4: J62.3, J63.3, J69.3, R35.1, U14.42
SDA5: J77.3, J78.3, J84.3, R43.1, U17.42
SIM_!CD!: J6.5, R8.1, SIM.2, U4.16
SIM_!CD!1: J23.5, R16.1, SIM1.2, U5.16
SIM_!CD!2: J38.5, R24.1, SIM2.2, U8.16
SIM_!CD!3: J53.5, R32.1, SIM3.2, U11.16
SIM_!CD!4: J68.5, R40.1, SIM4.2, U14.16
SIM_!CD!5: J83.5, R48.1, SIM5.2, U17.16
SIM_CLK: J6.4, J15.C3, U4.14
SIM_CLK1: J23.4, J27.C3, U5.14
SIM_CLK2: J38.4, J42.C3, U8.14
SIM_CLK3: J53.4, J57.C3, U11.14
SIM_CLK4: J68.4, J72.C3, U14.14
SIM_CLK5: J83.4, J87.C3, U17.14
SIM_IO: J6.3, J15.C7, U4.12
SIM_IO1: J23.3, J27.C7, U5.12
SIM_IO2: J38.3, J42.C7, U8.12
SIM_IO3: J53.3, J57.C7, U11.12
SIM_IO4: J68.3, J72.C7, U14.12
SIM_IO5: J83.3, J87.C7, U17.12
SIM_RST: J6.2, J15.C2, U4.10
SIM_RST1: J23.2, J27.C2, U5.10
SIM_RST2: J38.2, J42.C2, U8.10
SIM_RST3: J53.2, J57.C2, U11.10
SIM_RST4: J68.2, J72.C2, U14.10
SIM_RST5: J83.2, J87.C2, U17.10
SIM_VCC: J6.1, J15.C1, R8.2, U4.8
SIM_VCC1: J23.1, J27.C1, R16.2, U5.8
SIM_VCC2: J38.1, J42.C1, R24.2, U8.8
SIM_VCC3: J53.1, J57.C1, R32.2, U11.8
SIM_VCC4: J68.1, J72.C1, R40.2, U14.8
SIM_VCC5: J83.1, J87.C1, R48.2, U17.8
TX: J2.2, U4.64
TX1: J29.2, U5.64
TX2: J44.2, U8.64
TX3: J59.2, U11.64
TX4: J74.2, U14.64
TX5: J89.2, U17.64
USB_D+: J1.A6, J1.B6, U4.7
USB_D+1: J11.A6, J11.B6, U5.7
USB_D+2: J31.A6, J31.B6, U8.7
USB_D+3: J46.A6, J46.B6, U11.7
USB_D+4: J61.A6, J61.B6, U14.7
USB_D+5: J76.A6, J76.B6, U17.7
USB_D-: J1.A7, J1.B7, U4.9
USB_D-1: J11.A7, J11.B7, U5.9
USB_D-2: J31.A7, J31.B7, U8.9
USB_D-3: J46.A7, J46.B7, U11.9
USB_D-4: J61.A7, J61.B7, U14.9
USB_D-5: J76.A7, J76.B7, U17.9
VACT_GPS_IN: JP2.2, U4.22
VACT_GPS_IN1: JP4.2, U5.22
VACT_GPS_IN2: JP6.2, U8.22
VACT_GPS_IN3: JP8.2, U11.22
VACT_GPS_IN4: JP10.2, U14.22
VACT_GPS_IN5: JP12.2, U17.22
VACT_GPS_OUT: JP2.1, U4.20
VACT_GPS_OUT1: JP4.1, U5.20
VACT_GPS_OUT2: JP6.1, U8.20
VACT_GPS_OUT3: JP8.1, U11.20
VACT_GPS_OUT4: JP10.1, U14.20
VACT_GPS_OUT5: JP12.1, U17.20
VIN: C5.1, C6.1, C7.1, C8.A, C17.1, J5.1, J5.2, J5.3, J5.4, J5.5, MEAS.2, MEAS.4, U1.1, U1.3, U4.70, U4.72, U4.74, VIN_LED.2
VIN1: D1.C, D4.C, D6.C, MEAS.1, MEAS.3
VIN2: C9.1, C10.1, C11.1, C12.A, C13.1, J30.1, J30.2, J30.3, J30.4, J30.5, MEAS1.2, MEAS1.4, U5.70, U5.72, U5.74, U6.1, U6.3, VIN_LED1.2
VIN3: D8.C, D9.C, D10.C, MEAS1.1, MEAS1.3
VIN4: C19.1, C20.1, C21.1, C22.A, C23.1, J45.1, J45.2, J45.3, J45.4, J45.5, MEAS2.2, MEAS2.4, U8.70, U8.72, U8.74, U9.1, U9.3, VIN_LED2.2
VIN5: D13.C, D14.C, D15.C, MEAS2.1, MEAS2.3
VIN6: C27.1, C28.1, C29.1, C30.A, C31.1, J60.1, J60.2, J60.3, J60.4, J60.5, MEAS3.2, MEAS3.4, U11.70, U11.72, U11.74, U12.1, U12.3, VIN_LED3.2
VIN7: D18.C, D19.C, D20.C, MEAS3.1, MEAS3.3
VIN8: C35.1, C36.1, C37.1, C38.A, C39.1, J75.1, J75.2, J75.3, J75.4, J75.5, MEAS4.2, MEAS4.4, U14.70, U14.72, U14.74, U15.1, U15.3, VIN_LED4.2
VIN9: D23.C, D24.C, D25.C, MEAS4.1, MEAS4.3
VIN10: C43.1, C44.1, C45.1, C46.A, C47.1, J90.1, J90.2, J90.3, J90.4, J90.5, MEAS5.2, MEAS5.4, U17.70, U17.72, U17.74, U18.1, U18.3, VIN_LED5.2
VIN11: D28.C, D29.C, D30.C, MEAS5.1, MEAS5.3
VIO: C18.1, U1.5, U4.2, U4.4
VIO1: C14.1, U5.2, U5.4, U6.5
VIO2: C24.1, U8.2, U8.4, U9.5
VIO3: C32.1, U11.2, U11.4, U12.5
VIO4: C40.1, U14.2, U14.4, U15.5
VIO5: C48.1, U17.2, U17.4, U18.5
V_BATT: C4.1, D4.A, J4.2, J7.1, U2.3
V_BATT1: C1.1, D9.A, J19.2, J20.1, U3.3
V_BATT2: C15.1, D14.A, J34.2, J35.1, U7.3
V_BATT3: C25.1, D19.A, J49.2, J50.1, U10.3
V_BATT4: C33.1, D24.A, J64.2, J65.1, U13.3
V_BATT5: C41.1, D29.A, J79.2, J80.1, U16.3
V_USB: C3.1, D1.A, D2.A, J1.VBUS1, J1.VBUS2, U2.4, U4.13
V_USB1: C2.1, D3.A, D8.A, J11.VBUS1, J11.VBUS2, U3.4, U5.13
V_USB2: C16.1, D11.A, D13.A, J31.VBUS1, J31.VBUS2, U7.4, U8.13
V_USB3: C26.1, D16.A, D18.A, J46.VBUS1, J46.VBUS2, U10.4, U11.13
V_USB4: C34.1, D21.A, D23.A, J61.VBUS1, J61.VBUS2, U13.4, U14.13
V_USB5: C42.1, D26.A, D28.A, J76.VBUS1, J76.VBUS2, U16.4, U17.13

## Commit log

2021-06-15 Fix Notecard FP. Add VIO vreg. x02 release.
2021-06-15 Remove old files. Add readme and ignore.
2021-06-21 Change to 22uF cap. Add production files.
2021-06-21 Add production files.
2021-08-29 Change R8 to DNP.
2021-08-29 Update readme.
2021-12-20 Add dimensionals
2022-07-06 Updating readme with Notecard links
    Adds links to Notecard API documentation, and hardware design documentation.
2022-07-06 Remove documents directory
    Removes documents directory, which pointed to outdated information
2022-07-06 Update readme with datasheet link
    Adds link to Notecard datasheet

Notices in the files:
parts and their libraries:
SparkFun-Aesthetics: Licensing: Creative Commons ShareAlike 4.0 International - https://creativecommons.org/licenses/by-sa/4.0
SparkFun-Aesthetics: Released under the Creative Commons Attribution Share-Alike 4.0 License
SparkFun-Aesthetics: https://creativecommons.org/licenses/by-sa/4.0
